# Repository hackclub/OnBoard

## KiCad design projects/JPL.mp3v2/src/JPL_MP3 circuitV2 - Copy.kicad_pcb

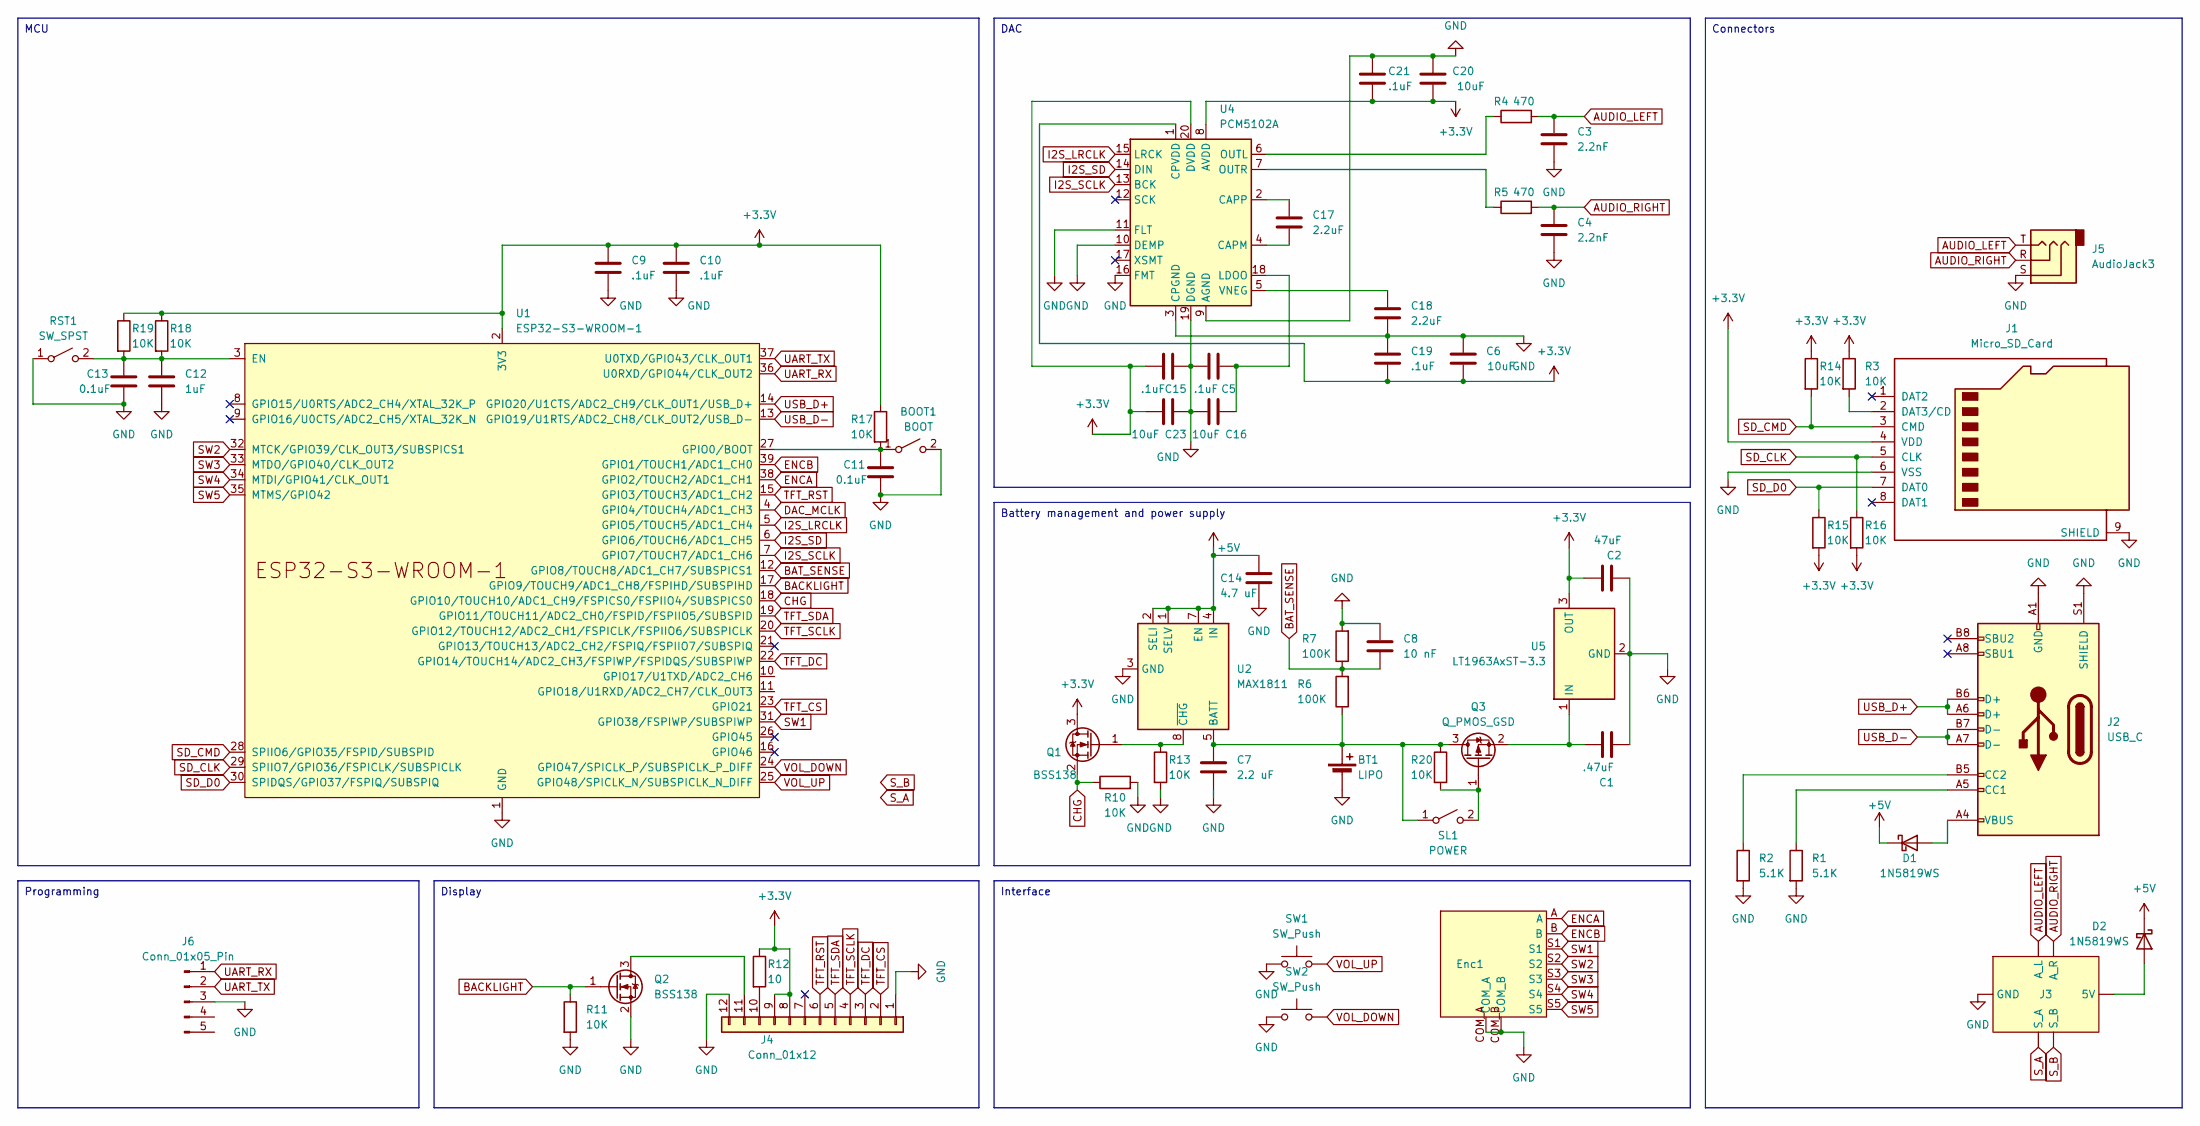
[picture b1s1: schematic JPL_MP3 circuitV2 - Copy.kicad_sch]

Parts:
BOOT1: BOOT; SW_SPST_B3U-1000P
BT1: LIPO
C1: .47uF; C_0603_1608Metric_Pad1.08x0.95mm_HandSolder
C2: 47uF; C_1210_3225Metric
C3, C4: 2.2nF; C_0603_1608Metric
C5, C9, C10, C15, C19, C21: .1uF; C_0603_1608Metric
C6, C16, C20, C23: 10uF; C_0603_1608Metric
C7: 2.2 uF; C_0603_1608Metric
C8: 10 nF; C_0603_1608Metric
C11, C13: 0.1uF; C_0603_1608Metric
C12: 1uF; C_0603_1608Metric
C14: 4.7 uF; C_0603_1608Metric
C17, C18: 2.2uF; C_0603_1608Metric
D1, D2: 1N5819WS; D_SOD-323
Enc1: ANO Rotary Encoder
J1: Micro_SD_Card; microSD_HC_Molex_104031-0811
J2: USB_C; USB_C_Receptacle_G-Switch_GT-USB-7010ASV
J3: (no value)
J4: Conn_01x12; TE_1-1734839-2_1x12-1MP_P0.5mm_Horizontal
J5: AudioJack3; Jack_3.5mm_KoreanHropartsElec_PJ-320D-4A_Horizontal
J6: Conn_01x05_Pin; Positive_Altitude_SWD_Connector
Q1, Q2: BSS138; SOT-23
Q3: Q_PMOS_GSD; SOT-23
R1, R2: 5.1K; R_0603_1608Metric
R3, R10, R11, R13, R14, R15, R16, R17, R18, R19, R20: 10K; R_0603_1608Metric
R4, R5: 470; R_0603_1608Metric
R6, R7: 100K; R_0603_1608Metric
R12: 10; R_0603_1608Metric
RST1: SW_SPST; SW_SPST_B3U-1000P
SL1: POWER; SW_SPDT_PCM12
SW1, SW2: SW_Push; SW_Push_1P1T-MP_NO_Horizontal_Alps_SKRTLAE010
U1: ESP32-S3-WROOM-1
U2: MAX1811; SOIC-8_3.9x4.9mm_P1.27mm
U4: PCM5102A; TSSOP-20_4.4x6.5mm_P0.65mm
U5: LT1963AxST-3.3; SOT-223-3_TabPin2

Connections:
+3.3V: C2.1, C6.1, C9.1, C10.1, C15.1, C19.2, C20.1, C21.2, C23.1, J1.4 (VDD), J4.8, J4.9, Q1.3 (D), R3.1, R12.1, R14.1, R15.2, R16.2, R17.1, R18.1, R19.1, U1.2 (3V3), U4.1 (CPVDD), U4.8 (AVDD), U4.20 (DVDD), U5.3 (OUT)
+5V: C14.1, D1.1 (K), D2.1 (K), U2.1 (SELV), U2.2 (SELI), U2.4 (IN), U2.7 (EN)
AUDIO_LEFT: C3.1, J3., J5.T, R4.2
AUDIO_RIGHT: C4.1, J3., J5.R, R5.2
BACKLIGHT: Q2.1 (G), R11.1, U1.17 (GPIO9/TOUCH9/ADC1_CH8/FSPIHD/SUBSPIHD)
BAT_SENSE: C8.2, R6.2, R7.1, U1.12 (GPIO8/TOUCH8/ADC1_CH7/SUBSPICS1)
CHG: Q1.2 (S), R10.1, U1.18 (GPIO10/TOUCH10/ADC1_CH9/FSPICS0/FSPIIO4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)
DAC_MCLK: U1.4 (GPIO4/TOUCH4/ADC1_CH3)
ENCA: Enc1.A, U1.38 (GPIO2/TOUCH2/ADC1_CH1)
ENCB: Enc1.B, U1.39 (GPIO1/TOUCH1/ADC1_CH0)
GND: BOOT1.2 (B), BT1.2 (-), C1.2, C2.2, C3.2, C4.2, C5.1, C6.2, C7.2, C8.1, C9.2, C10.2, C11.2, C12.2, C13.2, C14.2, C15.2, C16.1, C18.2, C19.1, C20.2, C21.1, C23.2, Enc1.COM_A, Enc1.COM_B, J1.6 (VSS), J1.9 (SHIELD), J2.A1 (GND), J2.A12 (GND), J2.B1 (GND), J2.B12 (GND), J2.S1 (SHIELD), J3., J4.1, J4.12, J5.S, J6.3, Q2.2 (S), R1.2, R2.2, R7.2, R10.2, R11.2, R13.2, RST1.1 (A), SW1.1, SW2.1, U1.1 (GND), U1.40 (GND), U1.41 (GND), U2.3 (GND), U2.6 (GND), U4.3 (CPGND), U4.9 (AGND), U4.10 (DEMP), U4.11 (FLT), U4.16 (FMT), U4.19 (DGND), U5.2 (GND); also elsewhere on the board
I2S_LRCLK: U1.5 (GPIO5/TOUCH5/ADC1_CH4), U4.15 (LRCK)
I2S_SCLK: U1.7 (GPIO7/TOUCH7/ADC1_CH6), U4.13 (BCK)
I2S_SD: U1.6 (GPIO6/TOUCH6/ADC1_CH5), U4.14 (DIN)
unnamed 14: BOOT1.1 (A), C11.1, R17.2, U1.27 (GPIO0/BOOT); also elsewhere on the board
unnamed 15: BT1.1 (+), C7.1, Q3.3 (D), R6.1, R20.1, SL1.1 (A), U2.5 (BATT); also elsewhere on the board
unnamed: D1.2 (A), J2.A4 (VBUS), J2.A9 (VBUS), J2.B4 (VBUS), J2.B9 (VBUS)
unnamed: D2.2 (A), J3.
unnamed: J1.2 (DAT3/CD), R3.2
unnamed: J2.A5 (CC1), R1.1
unnamed: J2.B5 (CC2), R2.1
unnamed: J4.10, R12.2
unnamed: J4.11, Q2.3 (D)
unnamed: Q1.1 (G), R13.1, U2.8 (~CHG)
unnamed: Q3.1 (G), R20.2, SL1.2 (B)
unnamed: C1.1, Q3.2 (S), U5.1 (IN)
unnamed 26: C12.1, C13.1, R18.2, R19.2, RST1.2 (B), U1.3 (EN); also elsewhere on the board
unnamed: C17.2, U4.4 (CAPM)
unnamed: C17.1, U4.2 (CAPP)
unnamed: C5.2, C16.2, U4.18 (LDOO)
unnamed: R4.1, U4.6 (OUTL)
unnamed: R5.1, U4.7 (OUTR)
unnamed: C18.1, U4.5 (VNEG)
SD_CLK: J1.5 (CLK), R16.1, U1.29 (SPIIO7/GPIO36/FSPICLK/SUBSPICLK)
SD_CMD: J1.3 (CMD), R14.2, U1.28 (SPIIO6/GPIO35/FSPID/SUBSPID)
SD_D0: J1.7 (DAT0), R15.1, U1.30 (SPIDQS/GPIO37/FSPIQ/SUBSPIQ)
SW1: Enc1.S1, U1.31 (GPIO38/FSPIWP/SUBSPIWP)
SW2: Enc1.S2, U1.32 (MTCK/GPIO39/CLK_OUT3/SUBSPICS1)
SW3: Enc1.S3, U1.33 (MTDO/GPIO40/CLK_OUT2)
SW4: Enc1.S4, U1.34 (MTDI/GPIO41/CLK_OUT1)
SW5: Enc1.S5, U1.35 (MTMS/GPIO42)
TFT_CS: J4.2, U1.23 (GPIO21)
TFT_DC: J4.3, U1.22 (GPIO14/TOUCH14/ADC2_CH3/FSPIWP/FSPIDQS/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)
TFT_RST: J4.6, U1.15 (GPIO3/TOUCH3/ADC1_CH2)
TFT_SCLK: J4.4, U1.20 (GPIO12/TOUCH12/ADC2_CH1/FSPICLK/FSPIIO6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)
TFT_SDA: J4.5, U1.19 (GPIO11/TOUCH11/ADC2_CH0/FSPID/FSPIIO5/S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)
UART_RX: J6.1, U1.36 (U0RXD/GPIO44/CLK_OUT2)
UART_TX: J6.2, U1.37 (U0TXD/GPIO43/CLK_OUT1)
USB_D+: J2.A6 (D+), J2.B6 (D+), U1.14 (GPIO20/U1CTS/ADC2_CH9/CLK_OUT1/USB_D+)
USB_D-: J2.A7 (D-), J2.B7 (D-), U1.13 (GPIO19/U1RTS/ADC2_CH8/CLK_OUT2/USB_D-)
VOL_DOWN: SW2.2, U1.24 (GPIO47/SPICLK_P/SUBSPICLK_P_DIFF)
VOL_UP: SW1.2, U1.25 (GPIO48/SPICLK_N/SUBSPICLK_N_DIFF)

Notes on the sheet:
Interface
Display
DAC
Connectors
Battery management and power supply
Programming
MCU

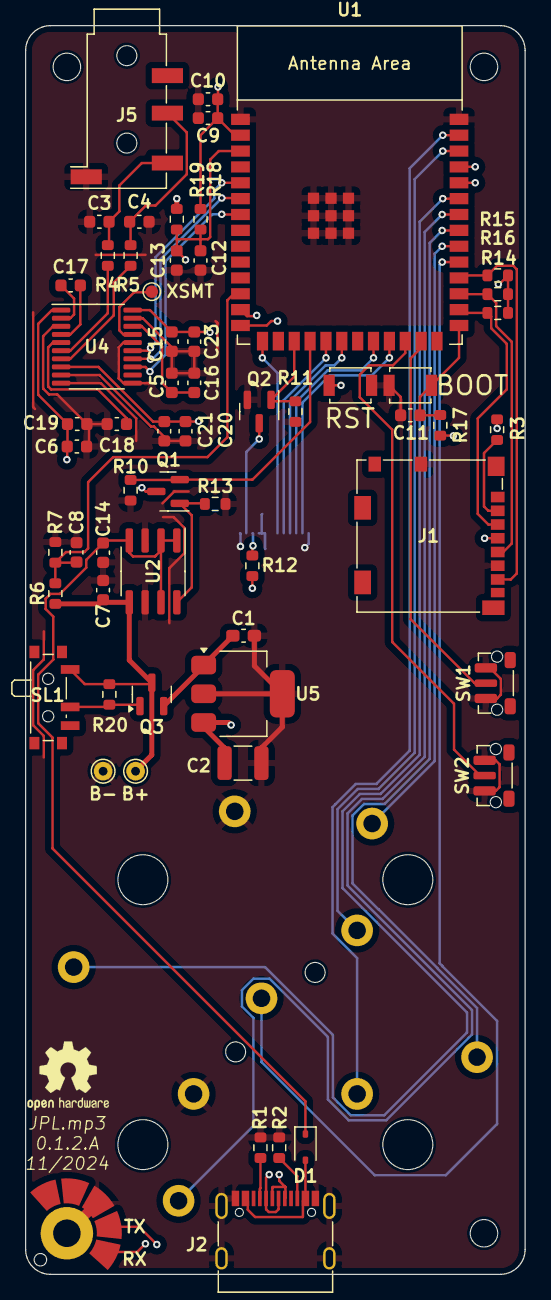
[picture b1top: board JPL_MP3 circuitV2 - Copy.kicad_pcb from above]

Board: 4 copper layers, 40.0 x 100.0 mm, 61 parts (1 on the bottom side), 50 nets.

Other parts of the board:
B+: TestPoint_THTPad_D1.5mm_Drill0.7mm
B-: TestPoint_THTPad_D1.5mm_Drill0.7mm
BOOT: BOOT; SW_SPST_B3U-1000P
RST: SW_SPST; SW_SPST_B3U-1000P

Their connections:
GND: B-.1, BOOT.2 (B), RST.1 (A); also elsewhere on the board
unnamed 14: BOOT.1 (A); also elsewhere on the board
unnamed 15: B+.1; also elsewhere on the board
unnamed 26: RST.2 (B); also elsewhere on the board

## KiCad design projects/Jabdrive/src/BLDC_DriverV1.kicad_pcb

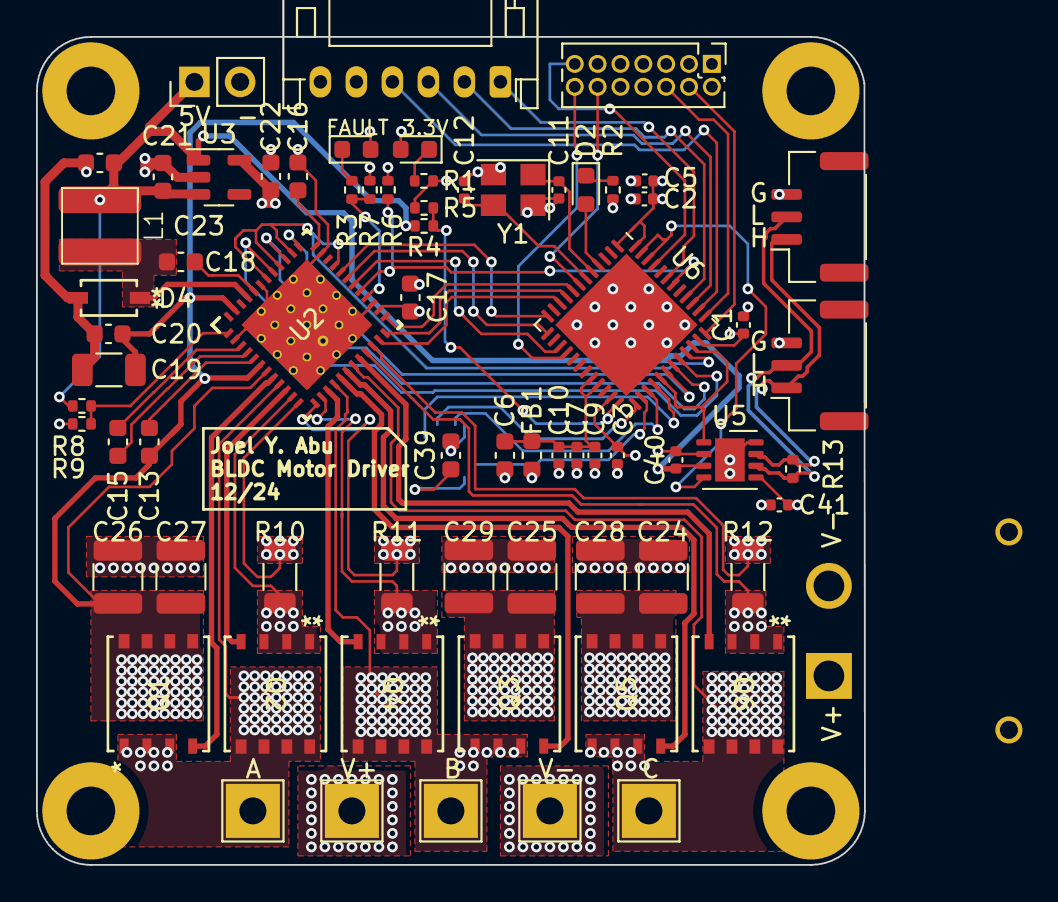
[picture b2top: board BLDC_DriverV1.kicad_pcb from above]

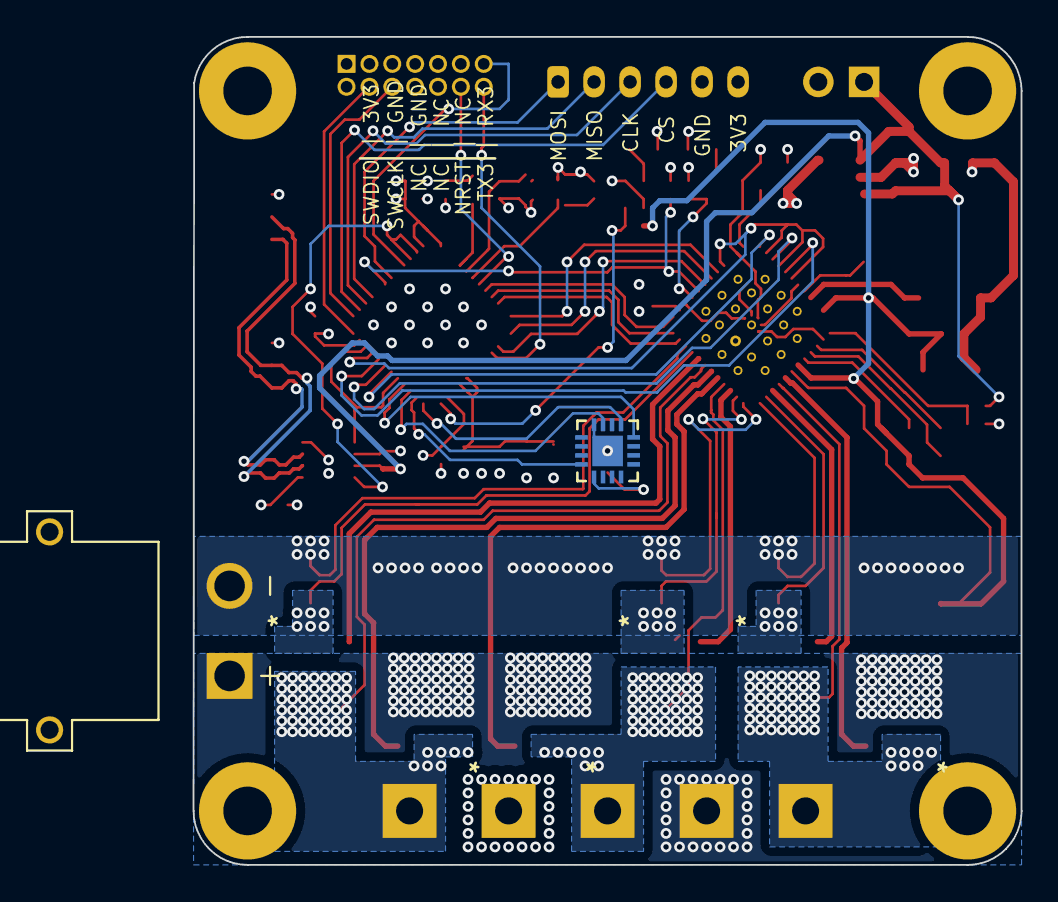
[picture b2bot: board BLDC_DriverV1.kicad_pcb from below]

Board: 4 copper layers, 46.0 x 46.0 mm, 75 parts (2 on the bottom side), 61 nets.

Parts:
C1, C2, C3, C7, C9, C40, C41: 100nF; C_0402_1005Metric
C5, C10: 4.7uF; C_0402_1005Metric
C6, C13, C16, C22, C23, C39: 1uF 50V; C_0603_1608Metric
C11, C12: 10pF; C_0402_1005Metric
C15: 47nF 50V; C_0603_1608Metric
C17, C18, C20: 100nF 50V; C_0603_1608Metric
C19: 10uF 50V; C_1206_3216Metric
C21: 22uF 10V; C_0603_1608Metric
C24, C25, C26, C27, C28, C29: 10uF 50V; C_1210_3225Metric
D1, D2: BLUE; LED_0603_1608Metric
D3: RED; LED_0603_1608Metric
D4: D_Schottky; SOD123_DIO
FB1: L_0603_1608Metric
H1, H2, H3, H4: MountingHole; MountingHole_2.7mm_M2.5_Pad
J1, J2, J3: Conn_01x01; TestPoint_THTPad_3.0x3.0mm_Drill1.5mm
J4: Conn_01x02; AMASS_XT30PW-M
J5: Conn_01x06_Pin; JST_PH_S6B-PH-K_1x06_P2.00mm_Horizontal
J6, J7: Conn_01x03; JST_GH_SM03B-GHS-TB_1x03-1MP_P1.25mm_Horizontal
J8: Conn_01x02_Pin; PinHeader_1x02_P2.54mm_Vertical
J9: Conn_02x07_Odd_Even; PinHeader_2x07_P1.27mm_Vertical
J10, J11: Conn_01x01_Pin; TestPoint_THTPad_3.0x3.0mm_Drill1.5mm
L1: 22uH; PIS3D18P
Q1, Q2, Q3, Q4, Q5, Q6: BSC0702LSATMA1; PG-TDSON-8-7
R1, R2: 15r; R_0402_1005Metric
R3: 56r; R_0402_1005Metric
R4: 110k 1%; R_0402_1005Metric
R5, R6, R7, R9: 10k 1%; R_0402_1005Metric
R8: 54.9k 1%; R_0402_1005Metric
R10, R11, R12: R_Shunt 1mOhm; R_1206_3216Metric
R13: 120r; R_0402_1005Metric
U2: DRV8323RSRGZT; RGZ0048A
U3: LP5907MFX-3.3; SOT-23-5
U4: MA702GQ-P; QFN-3x3_MA702_MNP
U5: TCAN1057ADRQ1; VSON-8-1EP_3x3mm_P0.65mm_EP1.65x2.4mm
U6: STM32G431CBUx; QFN-48-1EP_7x7mm_P0.5mm_EP5.6x5.6mm
Y1: Crystal_16MHz_10pF; Crystal_SMD_3225-4Pin_3.2x2.5mm

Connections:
+3.3V: C1.1, C2.1, C3.1, C5.1, C17.1, C22.1, C39.1, C41.1, D1.2 (A), D3.2 (A), FB1.2, J5.6, J9.3, R6.2, R7.2, U2.26 (VREF), U3.5 (OUT), U4.13 (VDD), U5.5 (VIO), U6.1 (VBAT), U6.23 (VDD), U6.35 (VDD), U6.48 (VDD)
+5V: C21.1, C23.1, C40.1, J8.1, L1.1, R8.2, U3.1 (IN), U3.3 (EN), U5.3 (VCC)
+BATT: C13.1, C19.1, C20.1, C24.1, C25.1, C26.1, C27.1, C28.1, C29.1, J4.P, J10.1, Q1.5 (D), Q1.6 (D), Q1.7 (D), Q1.8 (D), Q3.5 (D), Q3.6 (D), Q3.7 (D), Q3.8 (D), Q5.5 (D), Q5.6 (D), Q5.7 (D), Q5.8 (D), R4.2, U2.6 (VM), U2.7 (VDRAIN), U2.47 (VIN)
AGND: C1.2, C2.2, C3.2, C5.2, C6.2, C7.2, C9.2, C10.2, C11.2, C12.2, C16.1, C17.2, C19.2, C20.2, C21.2, C22.2, C23.2, C39.2, C40.2, C41.2, D4.2 (A), J5.5, J6.3, J7.3, J8.2, J9.5, J9.7, R1.1, R2.1, R5.1, R9.1, U2.27 (DGND), U2.35 (AGND), U2.43 (BGND), U3.2 (GND), U4.8 (GND), U4.17 (PAD), U5.2 (GND), U5.8 (S), U5.9, U6.49 (VSS), Y1.2, Y1.4
CAN1_RX: U5.4 (RXD), U6.46 (PB8), U6.47 (PB9)
CAN1_TX: U5.1 (TXD), U6.29 (PC6), U6.34 (PA12)
CAN_N: J6.2, J7.2, R13.1, U5.6 (CANL)
CAN_P: J6.1, J7.1, R13.2, U5.7 (CANH)
CUR1: U2.23 (SOC), U6.10 (PA2)
CUR2: U2.24 (SOB), U6.9 (PA1)
CUR3: U2.25 (SOA), U6.8 (PA0)
DRV_CS: U2.32 (GAIN), U6.12 (PA4)
DRV_FAULT: R3.2, R7.1, U2.28 (FAULT_N)
DRV_MISO: R6.1, U2.29 (MODE), U6.42 (PB4)
DRV_MOSI: U2.30 (IDRIVE), U6.15 (PA7)
DRV_SCK: U2.31 (VDS), U6.13 (PA5)
ENC_CS: U4.5 (CS), U6.25 (PB12)
ENC_MISO: U4.7 (MISO), U6.27 (PB14)
ENC_MOSI: U4.4 (MOSI), U6.28 (PB15)
ENC_SCK: U4.12 (SCLK), U6.26 (PB13)
GHA: Q1.4 (G), U2.8 (GHA)
GHB: Q3.4 (G), U2.17 (GHB)
GHC: Q5.4 (G), U2.18 (GHC)
GLA: Q2.4 (G), U2.10 (GLA)
GLB: Q4.4 (G), U2.15 (GLB)
GLC: Q6.4 (G), U2.20 (GLC)
HSE_IN: C11.1, U6.5 (PF0), Y1.1
HSE_OUT: C12.1, U6.6 (PF1), Y1.3
MOTOR_HIZ: U2.33 (ENABLE), U2.38 (INLA), U2.40 (INLB), U2.42 (INLC), U6.33 (PA11)
NRST: J9.12, U6.7 (PG10)
unnamed: D1.1 (K), R1.2
unnamed: D2.1 (K), R2.2
unnamed: D3.1 (K), R3.1
unnamed: C18.2, D4.1 (K), L1.2, U2.45 (SW)
unnamed: C18.1, U2.44 (CB)
unnamed: C15.2, U2.4 (CPH)
unnamed: C15.1, U2.3 (CPL)
unnamed: C16.2, U2.36 (DVDD)
unnamed: R8.1, R9.2, U2.1 (FB)
unnamed: C13.2, U2.5 (VCP)
PWM_A: U2.37 (INHA), U6.30 (PA8)
PWM_B: U2.39 (INHB), U6.31 (PA9)
PWM_C: U2.41 (INHC), U6.32 (PA10)
PWR_GND: C24.2, C25.2, C26.2, C27.2, C28.2, C29.2, J4.N, J11.1, R10.2, R11.2, R12.2, U2.2 (PGND), U2.12 (SNA), U2.13 (SNB), U2.22 (SNC), U2.49 (PAD)
RX1: J9.13, U6.45 (PB7)
SHA: J1.1, Q1.1 (S), Q1.2 (S), Q1.3 (S), Q2.5 (D), Q2.6 (D), Q2.7 (D), Q2.8 (D), U2.9 (SHA)
SHB: J2.1, Q3.1 (S), Q3.2 (S), Q3.3 (S), Q4.5 (D), Q4.6 (D), Q4.7 (D), Q4.8 (D), U2.16 (SHB)
SHC: J3.1, Q5.1 (S), Q5.2 (S), Q5.3 (S), Q6.5 (D), Q6.6 (D), Q6.7 (D), Q6.8 (D), U2.19 (SHC)
SPA: Q2.1 (S), Q2.2 (S), Q2.3 (S), R10.1, U2.11 (SPA)
SPB: Q4.1 (S), Q4.2 (S), Q4.3 (S), R11.1, U2.14 (SPB)
SPC: Q6.1 (S), Q6.2 (S), Q6.3 (S), R12.1, U2.21 (SPC)
SPI3_CLK: J5.3, U6.39 (PC10)
SPI3_CS: J5.4, U6.38 (PA15)
SPI3_MISO: J5.2, U6.40 (PC11)
SPI3_MOSI: J5.1, U6.43 (PB5)
SWCLK: J9.6, U6.37 (PA14)
SWDIO: J9.4, U6.36 (PA13)
TX1: J9.14, U6.16 (PC4)
USER_LED: D2.2 (A), U6.4 (PC15)
VDDA: C6.1, C7.1, C9.1, C10.1, FB1.1, U6.20 (VREF+), U6.21 (VDDA)
VIN_DIVIDER: R4.1, R5.2, U6.24 (PB11)

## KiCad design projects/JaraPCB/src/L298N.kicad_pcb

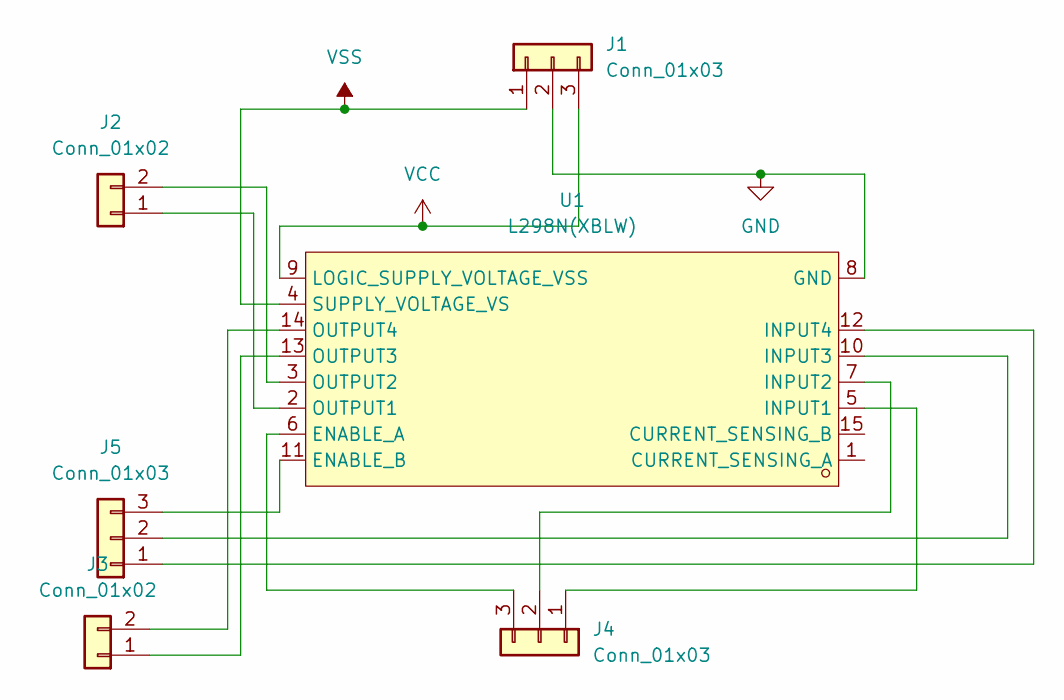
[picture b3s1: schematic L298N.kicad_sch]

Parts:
J1, J4, J5: Conn_01x03; TerminalBlock_Phoenix_MKDS-1,5-3-5.08_1x03_P5.08mm_Horizont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
J2, J3: Conn_01x02; TerminalBlock_Phoenix_MKDS-1,5-2-5.08_1x02_P5.08mm_Horizont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
U1: L298N(XBLW); SIP-15_L20.0-W4.6-P1.27-L; LCSC Part C18723576

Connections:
GND: J1.2, U1.8 (GND)
unnamed: J2.1, U1.2 (OUTPUT1)
unnamed: J2.2, U1.3 (OUTPUT2)
unnamed: J3.1, U1.13 (OUTPUT3)
unnamed: J3.2, U1.14 (OUTPUT4)
unnamed: J4.1, U1.5 (INPUT1)
unnamed: J4.2, U1.7 (INPUT2)
unnamed: J4.3, U1.6 (ENABLE_A)
unnamed: J5.1, U1.12 (INPUT4)
unnamed: J5.2, U1.10 (INPUT3)
unnamed: J5.3, U1.11 (ENABLE_B)
VCC: J1.3, U1.9 (LOGIC_SUPPLY_VOLTAGE_VSS)
VSS: J1.1, U1.4 (SUPPLY_VOLTAGE_VS)

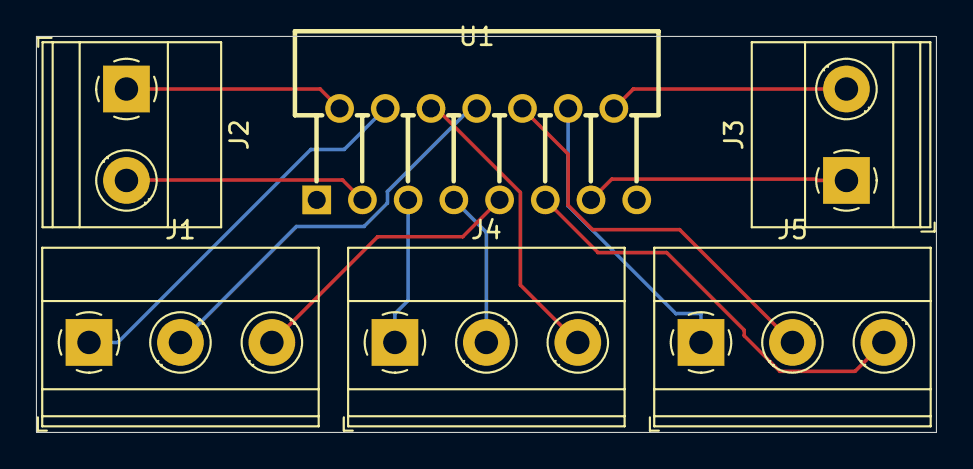
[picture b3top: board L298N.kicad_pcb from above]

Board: 2 copper layers, 50.0 x 22.0 mm, 6 parts (0 on the bottom side), 13 nets.

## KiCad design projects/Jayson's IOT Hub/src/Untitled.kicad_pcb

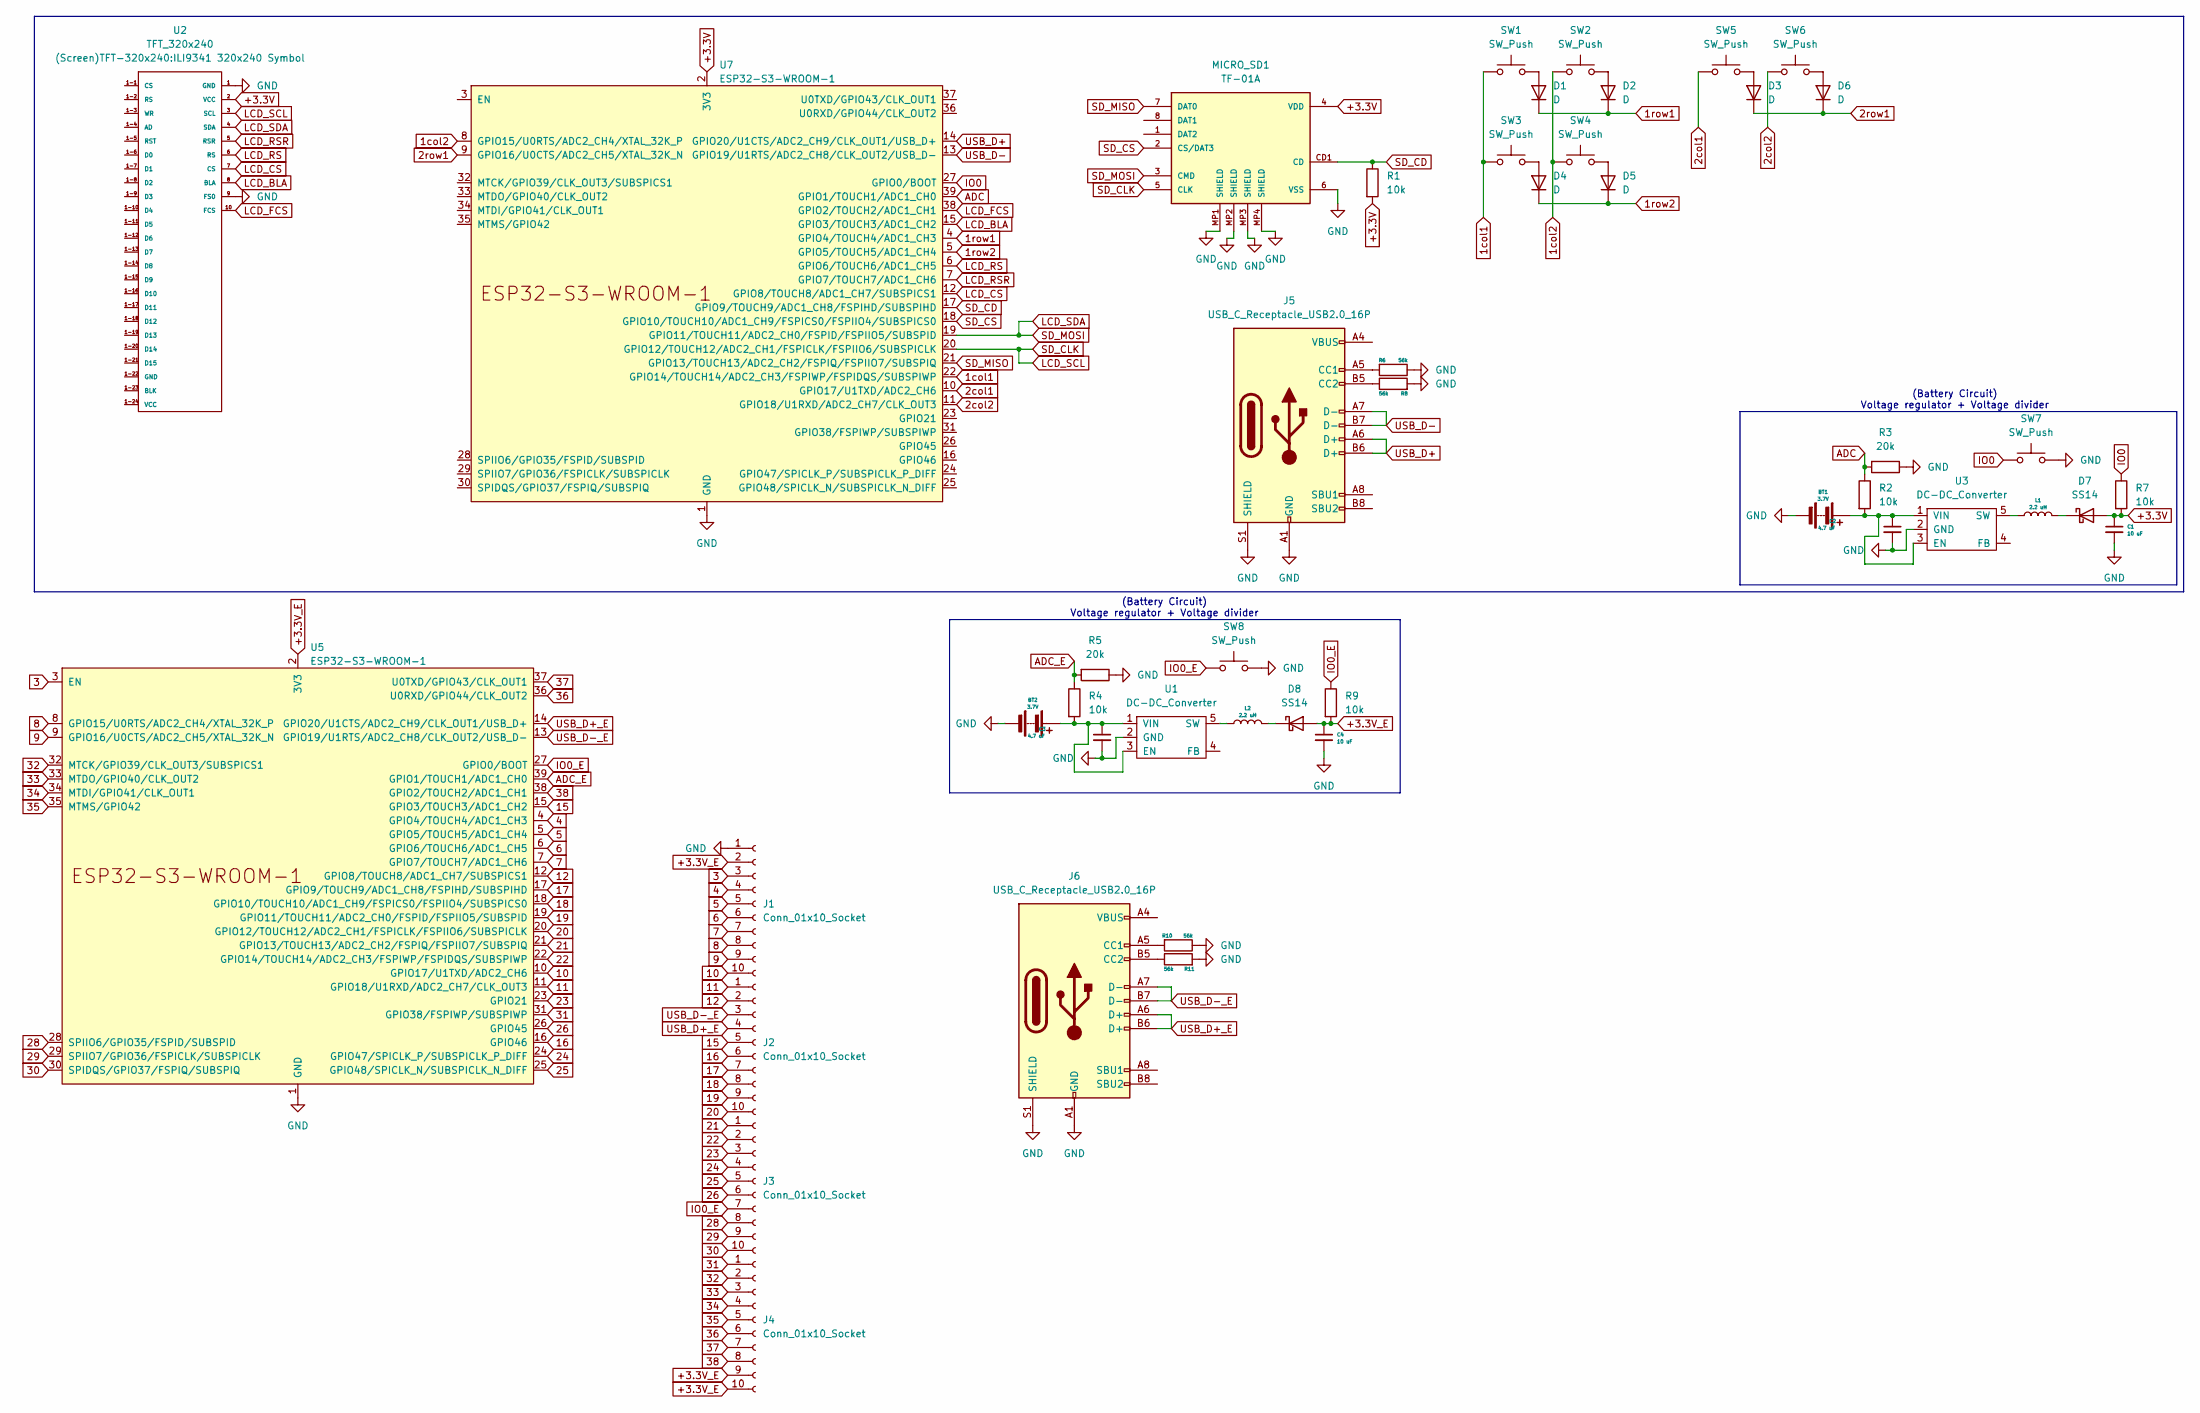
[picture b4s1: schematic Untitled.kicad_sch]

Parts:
BT1, BT2: 3.7V; BH-18650-B6AA002
C1, C4: 10 uF; CAPC2012X135N
C2, C3: 4.7 uF; CAPC2012X140N
D1, D2, D3, D4, D5, D6: D; ST(Semtech) 1N4148W
D7, D8: SS14; D_SMA
J1, J2, J3, J4: Conn_01x10_Socket; 1x10 conn
J5, J6: USB_C_Receptacle_USB2.0_16P; USB_C_Receptacle_HCTL_HC-TYPE-C-16P-01A
L1, L2: 2.2 uH; CDRH2D14NP-2R2NC
MICRO_SD1: TF-01A
R1, R2, R4, R7, R9: 10k; RESC1607X60N
R3, R5: 20k; RESC1607X60N
R6, R8, R10, R11: 56k; RESC1607X60N
SW1, SW2, SW3, SW4, SW5, SW6, SW7, SW8: SW_Push; SW_TS-1088-AR02016
U1, U3: DC-DC_Converter
U2: TFT_320x240; ILI9341 320x240 Symbol
U5, U7: ESP32-S3-WROOM-1

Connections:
1col1: SW1.1, SW3.1, U7.22 (GPIO14/TOUCH14/ADC2_CH3/FSPIWP/FSPIDQS/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)
1col2: SW2.1, SW4.1, U7.8 (GPIO15/U0RTS/ADC2_CH4/XTAL_32K_P)
1row1: D1.1 (K), D2.1 (K), U7.4 (GPIO4/TOUCH4/ADC1_CH3)
1row2: D4.1 (K), D5.1 (K), U7.5 (GPIO5/TOUCH5/ADC1_CH4)
2col1: SW5.1, U7.10 (GPIO17/U1TXD/ADC2_CH6)
2col2: SW6.1, U7.11 (GPIO18/U1RXD/ADC2_CH7/CLK_OUT3)
2row1: D3.1 (K), D6.1 (K), U7.9 (GPIO16/U0CTS/ADC2_CH5/XTAL_32K_N)
3: J1.3, U5.3 (EN)
4: J1.4, U5.4 (GPIO4/TOUCH4/ADC1_CH3)
5: J1.5, U5.5 (GPIO5/TOUCH5/ADC1_CH4)
6: J1.6, U5.6 (GPIO6/TOUCH6/ADC1_CH5)
7: J1.7, U5.7 (GPIO7/TOUCH7/ADC1_CH6)
8: J1.8, U5.8 (GPIO15/U0RTS/ADC2_CH4/XTAL_32K_P)
9: J1.9, U5.9 (GPIO16/U0CTS/ADC2_CH5/XTAL_32K_N)
10: J1.10, U5.10 (GPIO17/U1TXD/ADC2_CH6)
11: J2.1, U5.11 (GPIO18/U1RXD/ADC2_CH7/CLK_OUT3)
12: J2.2, U5.12 (GPIO8/TOUCH8/ADC1_CH7/SUBSPICS1)
15: J2.5, U5.15 (GPIO3/TOUCH3/ADC1_CH2)
16: J2.6, U5.16 (GPIO46)
17: J2.7, U5.17 (GPIO9/TOUCH9/ADC1_CH8/FSPIHD/SUBSPIHD)
18: J2.8, U5.18 (GPIO10/TOUCH10/ADC1_CH9/FSPICS0/FSPIIO4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)
19: J2.9, U5.19 (GPIO11/TOUCH11/ADC2_CH0/FSPID/FSPIIO5/S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)
20: J2.10, U5.20 (GPIO12/TOUCH12/ADC2_CH1/FSPICLK/FSPIIO6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)
21: J3.1, U5.21 (GPIO13/TOUCH13/ADC2_CH2/FSPIQ/FSPIIO7/S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)
22: J3.2, U5.22 (GPIO14/TOUCH14/ADC2_CH3/FSPIWP/FSPIDQS/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)
23: J3.3, U5.23 (GPIO21)
24: J3.4, U5.24 (GPIO47/SPICLK_P/SUBSPICLK_P_DIFF)
25: J3.5, U5.25 (GPIO48/SPICLK_N/SUBSPICLK_N_DIFF)
26: J3.6, U5.26 (GPIO45)
28: J3.8, U5.28 (SPIIO6/GPIO35/FSPID/SUBSPID)
29: J3.9, U5.29 (SPIIO7/GPIO36/FSPICLK/SUBSPICLK)
30: J3.10, U5.30 (SPIDQS/GPIO37/FSPIQ/SUBSPIQ)
31: J4.1, U5.31 (GPIO38/FSPIWP/SUBSPIWP)
32: J4.2, U5.32 (MTCK/GPIO39/CLK_OUT3/SUBSPICS1)
33: J4.3, U5.33 (MTDO/GPIO40/CLK_OUT2)
34: J4.4, U5.34 (MTDI/GPIO41/CLK_OUT1)
35: J4.5, U5.35 (MTMS/GPIO42)
36: J4.6, U5.36 (U0RXD/GPIO44/CLK_OUT2)
37: J4.7, U5.37 (U0TXD/GPIO43/CLK_OUT1)
38: J4.8, U5.38 (GPIO2/TOUCH2/ADC1_CH1)
+3.3V: C1.1, D7.2 (A), MICRO_SD1.4 (VDD), R1.2, R7.2, U2.2 (VCC), U7.2 (3V3)
+3.3V_E: C4.1, D8.2 (A), J1.2, J4.9, J4.10, R9.2, U5.2 (3V3)
ADC: R2.1, R3.2, U7.39 (GPIO1/TOUCH1/ADC1_CH0)
ADC_E: R4.1, R5.2, U5.39 (GPIO1/TOUCH1/ADC1_CH0)
GND: BT1.2 (-), BT2.2 (-), C1.2, C2.2, C3.2, C4.2, J1.1, J5.A1 (GND), J5.A12 (GND), J5.B1 (GND), J5.B12 (GND), J5.S1 (SHIELD), J6.A1 (GND), J6.A12 (GND), J6.B1 (GND), J6.B12 (GND), J6.S1 (SHIELD), MICRO_SD1.6 (VSS), MICRO_SD1.MP1 (SHIELD), MICRO_SD1.MP2 (SHIELD), MICRO_SD1.MP3 (SHIELD), MICRO_SD1.MP4 (SHIELD), R3.1, R5.1, R6.1, R8.2, R10.1, R11.2, SW7.2, SW8.2, U1.2 (GND), U2.1 (GND), U2.9 (FS0), U3.2 (GND), U5.1 (GND), U5.40 (GND), U5.41 (GND), U7.1 (GND), U7.40 (GND), U7.41 (GND)
IO0: R7.1, SW7.1, U7.27 (GPIO0/BOOT)
IO0_E: J3.7, R9.1, SW8.1, U5.27 (GPIO0/BOOT)
LCD_BLA: U2.8 (BLA), U7.15 (GPIO3/TOUCH3/ADC1_CH2)
LCD_CS: U2.7 (CS), U7.12 (GPIO8/TOUCH8/ADC1_CH7/SUBSPICS1)
LCD_FCS: U2.10 (FCS), U7.38 (GPIO2/TOUCH2/ADC1_CH1)
LCD_RS: U2.6 (RS), U7.6 (GPIO6/TOUCH6/ADC1_CH5)
LCD_RSR: U2.5 (RSR), U7.7 (GPIO7/TOUCH7/ADC1_CH6)
LCD_SCL: MICRO_SD1.5 (CLK), U2.3 (SCL), U7.20 (GPIO12/TOUCH12/ADC2_CH1/FSPICLK/FSPIIO6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)
LCD_SDA: MICRO_SD1.3 (CMD), U2.4 (SDA), U7.19 (GPIO11/TOUCH11/ADC2_CH0/FSPID/FSPIIO5/S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)
unnamed: BT1.1 (+), C2.1, R2.2, U3.1 (VIN), U3.3 (EN)
unnamed: BT2.1 (+), C3.1, R4.2, U1.1 (VIN), U1.3 (EN)
unnamed: D1.2 (A), SW1.2
unnamed: D2.2 (A), SW2.2
unnamed: D3.2 (A), SW5.2
unnamed: D4.2 (A), SW3.2
unnamed: D5.2 (A), SW4.2
unnamed: D6.2 (A), SW6.2
unnamed: D7.1 (K), L1.2
unnamed: D8.1 (K), L2.2
unnamed: J5.A5 (CC1), R6.2
unnamed: J5.B5 (CC2), R8.1
unnamed: J5.A4 (VBUS), J5.A9 (VBUS), J5.B4 (VBUS), J5.B9 (VBUS)
unnamed: J6.A5 (CC1), R10.2
unnamed: J6.B5 (CC2), R11.1
unnamed: J6.A4 (VBUS), J6.A9 (VBUS), J6.B4 (VBUS), J6.B9 (VBUS)
unnamed: L2.1, U1.5 (SW)
unnamed: L1.1, U3.5 (SW)
SD_CD: MICRO_SD1.CD1 (CD), R1.1, U7.17 (GPIO9/TOUCH9/ADC1_CH8/FSPIHD/SUBSPIHD)
SD_CS: MICRO_SD1.2 (CS/DAT3), U7.18 (GPIO10/TOUCH10/ADC1_CH9/FSPICS0/FSPIIO4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)
SD_MISO: MICRO_SD1.7 (DAT0), U7.21 (GPIO13/TOUCH13/ADC2_CH2/FSPIQ/FSPIIO7/S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)
USB_D+: J5.A6 (D+), J5.B6 (D+), U7.14 (GPIO20/U1CTS/ADC2_CH9/CLK_OUT1/USB_D+)
USB_D+_E: J2.4, J6.A6 (D+), J6.B6 (D+), U5.14 (GPIO20/U1CTS/ADC2_CH9/CLK_OUT1/USB_D+)
USB_D-: J5.A7 (D-), J5.B7 (D-), U7.13 (GPIO19/U1RTS/ADC2_CH8/CLK_OUT2/USB_D-)
USB_D-_E: J2.3, J6.A7 (D-), J6.B7 (D-), U5.13 (GPIO19/U1RTS/ADC2_CH8/CLK_OUT2/USB_D-)

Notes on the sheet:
(Battery Circuit) Voltage regulator + Voltage divider

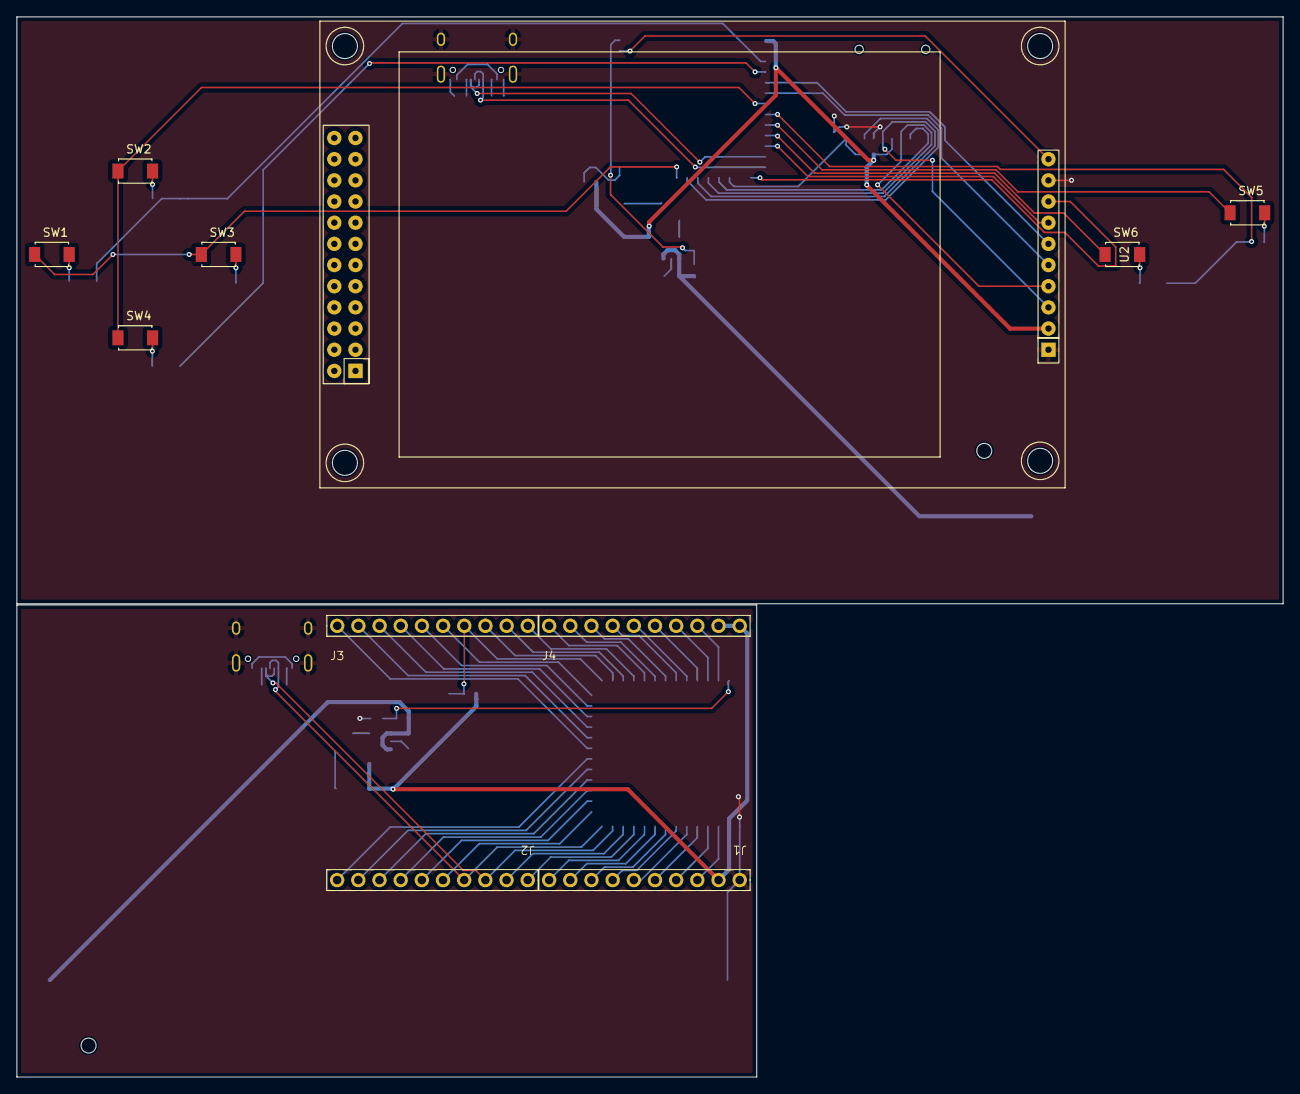
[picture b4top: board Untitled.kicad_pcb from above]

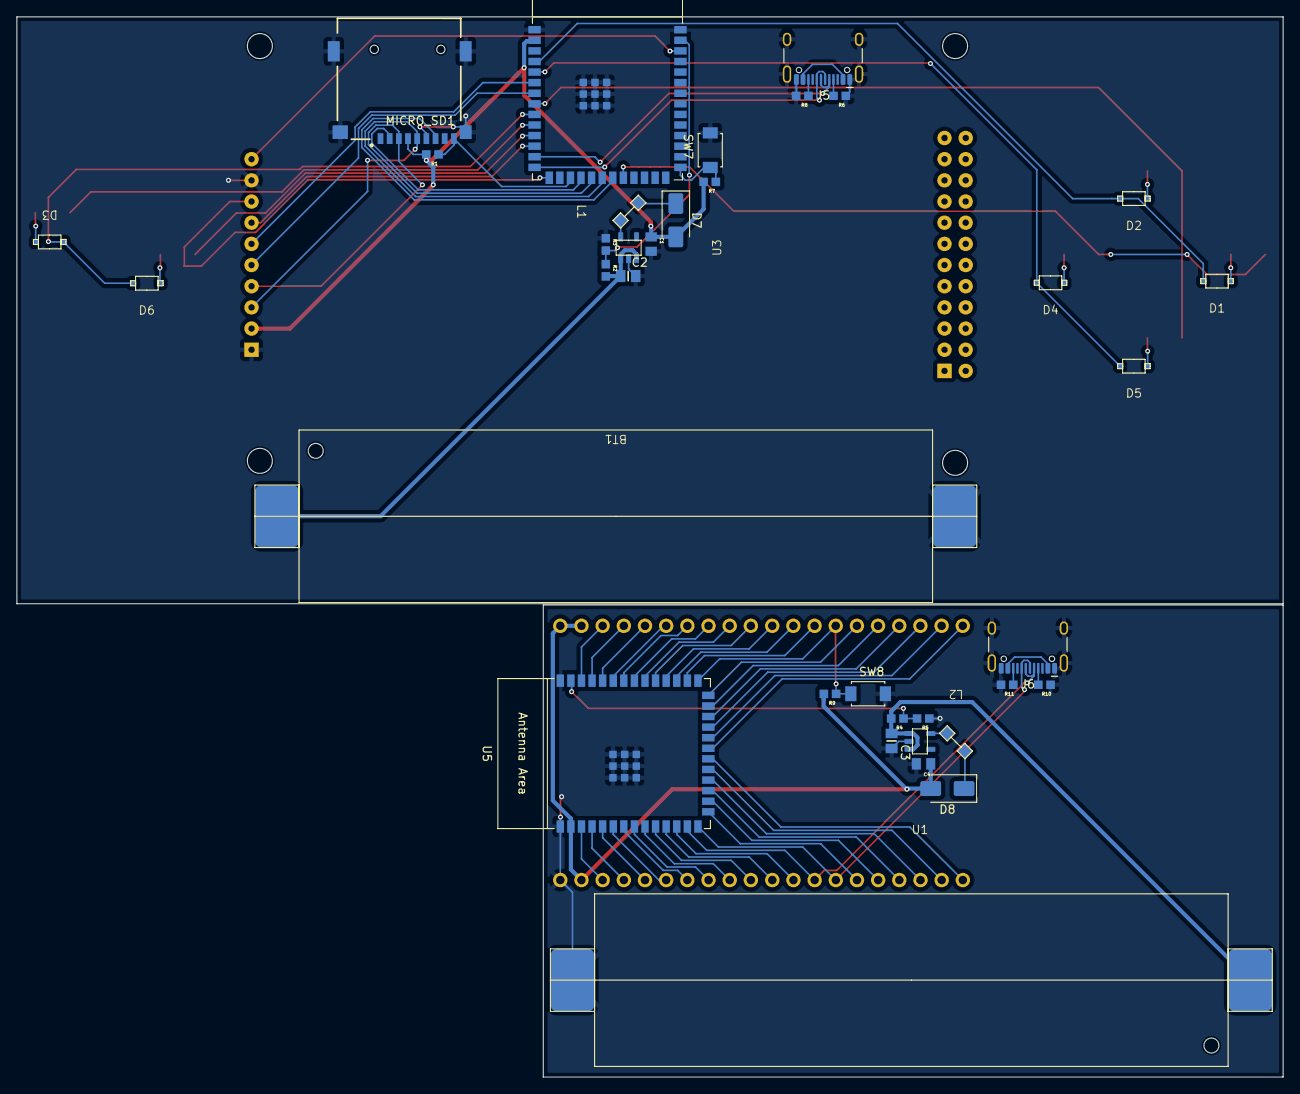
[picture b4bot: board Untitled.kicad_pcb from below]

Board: 2 copper layers, 151.9 x 127.2 mm, 47 parts (36 on the bottom side), 79 nets.

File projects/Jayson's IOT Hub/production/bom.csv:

Designator,Footprint,Quantity,Value,LCSC Part #
"BT1, BT2",BH-18650-B6AA002,2,3.7V,
"C1, C4",CAPC2012X135N,2,10 uF,
"C2, C3",CAPC2012X140N,2,4.7 uF,
"D1, D2, D3, D4, D5, D6",ST(Semtech) 1N4148W,6,D,
"D7, D8",D_SMA,2,SS14,
"J1, J2, J3, J4",1x10 conn,4,Conn_01x10_Socket,
"J5, J6",USB_C_Receptacle_HCTL_HC-TYPE-C-16P-01A,2,USB_C_Receptacle_USB2.0_16P,
"L1, L2",CDRH2D14NP-2R2NC,2,2.2 uH,
MICRO_SD1,TF-01A,1,TF-01A,
"R1, R2, R4, R7, R9",RESC1607X60N,5,10k,
"R10, R11, R6, R8",RESC1607X60N,4,56k,
"R3, R5",RESC1607X60N,2,20k,
"SW1, SW2, SW3, SW4, SW5, SW6, SW7, SW8",SW_TS-1088-AR02016,8,SW_Push,
"U1, U3",DC-DC_Converter,2,DC-DC_Converter,
U2,ILI9341 320x240 Symbol,1,TFT_320x240,
"U5, U7",ESP32-S3-WROOM-1,2,ESP32-S3-WROOM-1,
